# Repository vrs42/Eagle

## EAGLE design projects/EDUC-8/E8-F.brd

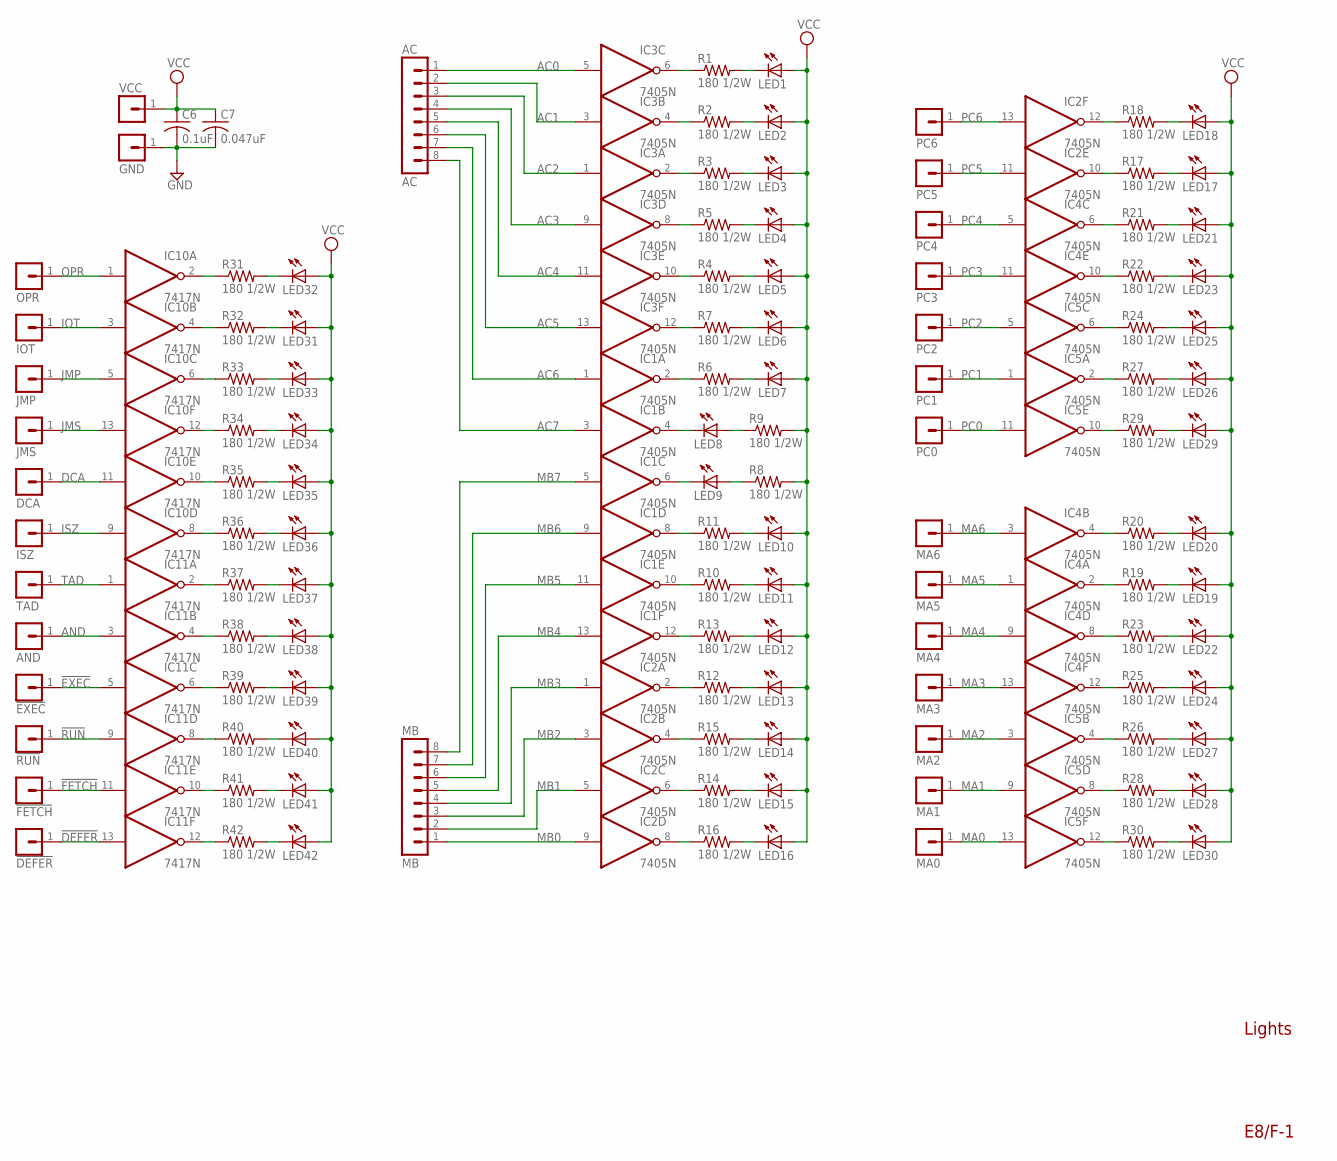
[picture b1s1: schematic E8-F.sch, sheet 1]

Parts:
!DEFER: MA01-1
!EXEC: MA01-1
!FETCH: MA01-1
!RUN: MA01-1
AC: AC; MA08-1
AND: MA01-1
C6: 0.1uF; C075-032X103
C7: 0.047uF; C075-032X103
DCA: MA01-1
GND: MA01-1
IC1, IC2, IC3, IC4, IC5: 7405N; DIL14
IC10, IC11: 7417N; DIL14
IOT: MA01-1
ISZ: MA01-1
JMP: MA01-1
JMS: MA01-1
LED1, LED2, LED3, LED4, LED5, LED6, LED7, LED8, LED9, LED10, LED11, LED12, LED13, LED14, LED15, LED16, LED17, LED18, LED19, LED20, LED21, LED22, LED23, LED24, LED25, LED26, LED27, LED28, LED29, LED30, LED31, LED32, LED33, LED34, LED35, LED36, LED37, LED38, LED39, LED40, LED41, LED42: LED5MM
MA0, MA1, MA2, MA3, MA4, MA5, MA6: MA01-1
MB: MB; MA08-1
OPR: MA01-1
PC0, PC1, PC2, PC3, PC4, PC5, PC6: MA01-1
R1, R2, R3, R5, R7, R10, R13, R14, R21, R28, R29, R30: 180 1/2W; 0309/.45
R4, R6, R8, R9, R12, R15, R16, R17, R18, R19, R24: 180 1/2W; 0309/12
R11: 180 1/2W; 0309/11
R20, R27: 180 1/2W; 0309/15
R22, R23, R25, R26, R39, R40, R41, R42: 180 1/2W; 0309/10
R31, R32, R33, R34, R35, R36, R37, R38: 180 1/2W; 0309/8
TAD: MA01-1
VCC: MA01-1

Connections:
!DEFER: !DEFER.1, IC11.13 (I)
!EXEC: !EXEC.1, IC11.5 (I)
!FETCH: !FETCH.1, IC11.11 (I)
!RUN: !RUN.1, IC11.9 (I)
AC0: AC.1, IC3.5 (I)
AC1: AC.2, IC3.3 (I)
AC2: AC.3, IC3.1 (I)
AC3: AC.4, IC3.9 (I)
AC4: AC.5, IC3.11 (I)
AC5: AC.6, IC3.13 (I)
AC6: AC.7, IC1.1 (I)
AC7: AC.8, IC1.3 (I)
AND: AND.1, IC11.3 (I)
DCA: DCA.1, IC10.11 (I)
GND: C6.2, C7.2, GND.1, IC1.7 (GND), IC2.7 (GND), IC3.7 (GND), IC4.7 (GND), IC5.7 (GND), IC10.7 (GND), IC11.7 (GND); also elsewhere on the board
IOT: IC10.3 (I), IOT.1
ISZ: IC10.9 (I), ISZ.1
JMP: IC10.5 (I), JMP.1
JMS: IC10.13 (I), JMS.1
MA0: IC5.13 (I), MA0.1
MA1: IC5.9 (I), MA1.1
MA2: IC5.3 (I), MA2.1
MA3: IC4.13 (I), MA3.1
MA4: IC4.9 (I), MA4.1
MA5: IC4.1 (I), MA5.1
MA6: IC4.3 (I), MA6.1
MB0: IC2.9 (I), MB.1
MB1: IC2.5 (I), MB.2
MB2: IC2.3 (I), MB.3
MB3: IC2.1 (I), MB.4
MB4: IC1.13 (I), MB.5
MB5: IC1.11 (I), MB.6
MB6: IC1.9 (I), MB.7
MB7: IC1.5 (I), MB.8
unnamed: IC2.12 (O), R18.1
unnamed: IC2.10 (O), R17.1
unnamed: IC3.6 (O), R1.1
unnamed: IC3.4 (O), R2.1
unnamed: IC3.2 (O), R3.1
unnamed: IC3.12 (O), R7.1
unnamed: LED7.K (C), R6.2
unnamed: LED12.K (C), R13.2
unnamed: IC1.10 (O), R10.1
unnamed: LED10.K (C), R11.2
unnamed: IC1.6 (O), LED9.K (C)
unnamed: LED8.A, R9.1
unnamed: IC1.2 (O), R6.1
unnamed: LED9.A, R8.1
unnamed: IC1.4 (O), LED8.K (C)
unnamed: IC1.8 (O), R11.1
unnamed: LED11.K (C), R10.2
unnamed: IC2.8 (O), R16.1
unnamed: LED13.K (C), R12.2
unnamed: LED18.K (C), R18.2
unnamed: LED17.K (C), R17.2
unnamed: LED16.K (C), R16.2
unnamed: LED15.K (C), R14.2
unnamed: LED14.K (C), R15.2
unnamed: IC2.6 (O), R14.1
unnamed: IC2.4 (O), R15.1
unnamed: IC2.2 (O), R12.1
unnamed: IC1.12 (O), R13.1
unnamed: IC3.10 (O), R4.1
unnamed: IC3.8 (O), R5.1
unnamed: LED1.K (C), R1.2
unnamed: LED6.K (C), R7.2
unnamed: LED5.K (C), R4.2
unnamed: LED4.K (C), R5.2
unnamed: LED3.K (C), R3.2
unnamed: LED2.K (C), R2.2
unnamed: LED25.K (C), R24.2
unnamed: LED19.K (C), R19.2
unnamed: LED24.K (C), R25.2
unnamed: LED23.K (C), R22.2
unnamed: LED22.K (C), R23.2
unnamed: LED21.K (C), R21.2
unnamed: IC5.6 (O), R24.1
unnamed: LED26.K (C), R27.2
unnamed: LED27.K (C), R26.2
unnamed: LED28.K (C), R28.2
unnamed: LED29.K (C), R29.2
unnamed: LED30.K (C), R30.2
unnamed: LED31.K (C), R32.2
unnamed: LED32.K (C), R31.2
unnamed: LED33.K (C), R33.2
unnamed: LED34.K (C), R34.2
unnamed: LED35.K (C), R35.2
unnamed: LED36.K (C), R36.2
unnamed: IC5.2 (O), R27.1
unnamed: IC5.12 (O), R30.1
unnamed: IC5.10 (O), R29.1
unnamed: IC5.8 (O), R28.1
unnamed: LED37.K (C), R37.2
unnamed: IC5.4 (O), R26.1
unnamed: LED40.K (C), R40.2
unnamed: LED39.K (C), R39.2
unnamed: LED38.K (C), R38.2
unnamed: LED42.K (C), R42.2
unnamed: LED41.K (C), R41.2
unnamed: IC10.2 (O), R31.1
unnamed: IC10.8 (O), R36.1
unnamed: IC10.10 (O), R35.1
unnamed: IC10.12 (O), R34.1
unnamed: IC10.6 (O), R33.1
unnamed: IC10.4 (O), R32.1
unnamed: IC11.2 (O), R37.1
unnamed: IC11.12 (O), R42.1
unnamed: IC11.10 (O), R41.1
unnamed: IC11.8 (O), R40.1
unnamed: IC11.6 (O), R39.1
unnamed: IC11.4 (O), R38.1
unnamed: LED20.K (C), R20.2
unnamed: IC4.2 (O), R19.1
unnamed: IC4.4 (O), R20.1
unnamed: IC4.6 (O), R21.1
unnamed: IC4.12 (O), R25.1
unnamed: IC4.10 (O), R22.1
unnamed: IC4.8 (O), R23.1
OPR: IC10.1 (I), OPR.1
PC0: IC5.11 (I), PC0.1
PC1: IC5.1 (I), PC1.1
PC2: IC5.5 (I), PC2.1
PC3: IC4.11 (I), PC3.1
PC4: IC4.5 (I), PC4.1
PC5: IC2.11 (I), PC5.1
PC6: IC2.13 (I), PC6.1
TAD: IC11.1 (I), TAD.1
VCC: C6.1, C7.1, IC1.14 (VCC), IC2.14 (VCC), IC3.14 (VCC), IC4.14 (VCC), IC5.14 (VCC), IC10.14 (VCC), IC11.14 (VCC), LED1.A, LED2.A, LED3.A, LED4.A, LED5.A, LED6.A, LED7.A, LED10.A, LED11.A, LED12.A, LED13.A, LED14.A, LED15.A, LED16.A, LED17.A, LED18.A, LED19.A, LED20.A, LED21.A, LED22.A, LED23.A, LED24.A, LED25.A, LED26.A, LED27.A, LED28.A, LED29.A, LED30.A, LED31.A, LED32.A, LED33.A, LED34.A, LED35.A, LED36.A, LED37.A, LED38.A, LED39.A, LED40.A, LED41.A, LED42.A, R8.2, R9.2, VCC.1; also elsewhere on the board

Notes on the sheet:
Lights
E8/F-1

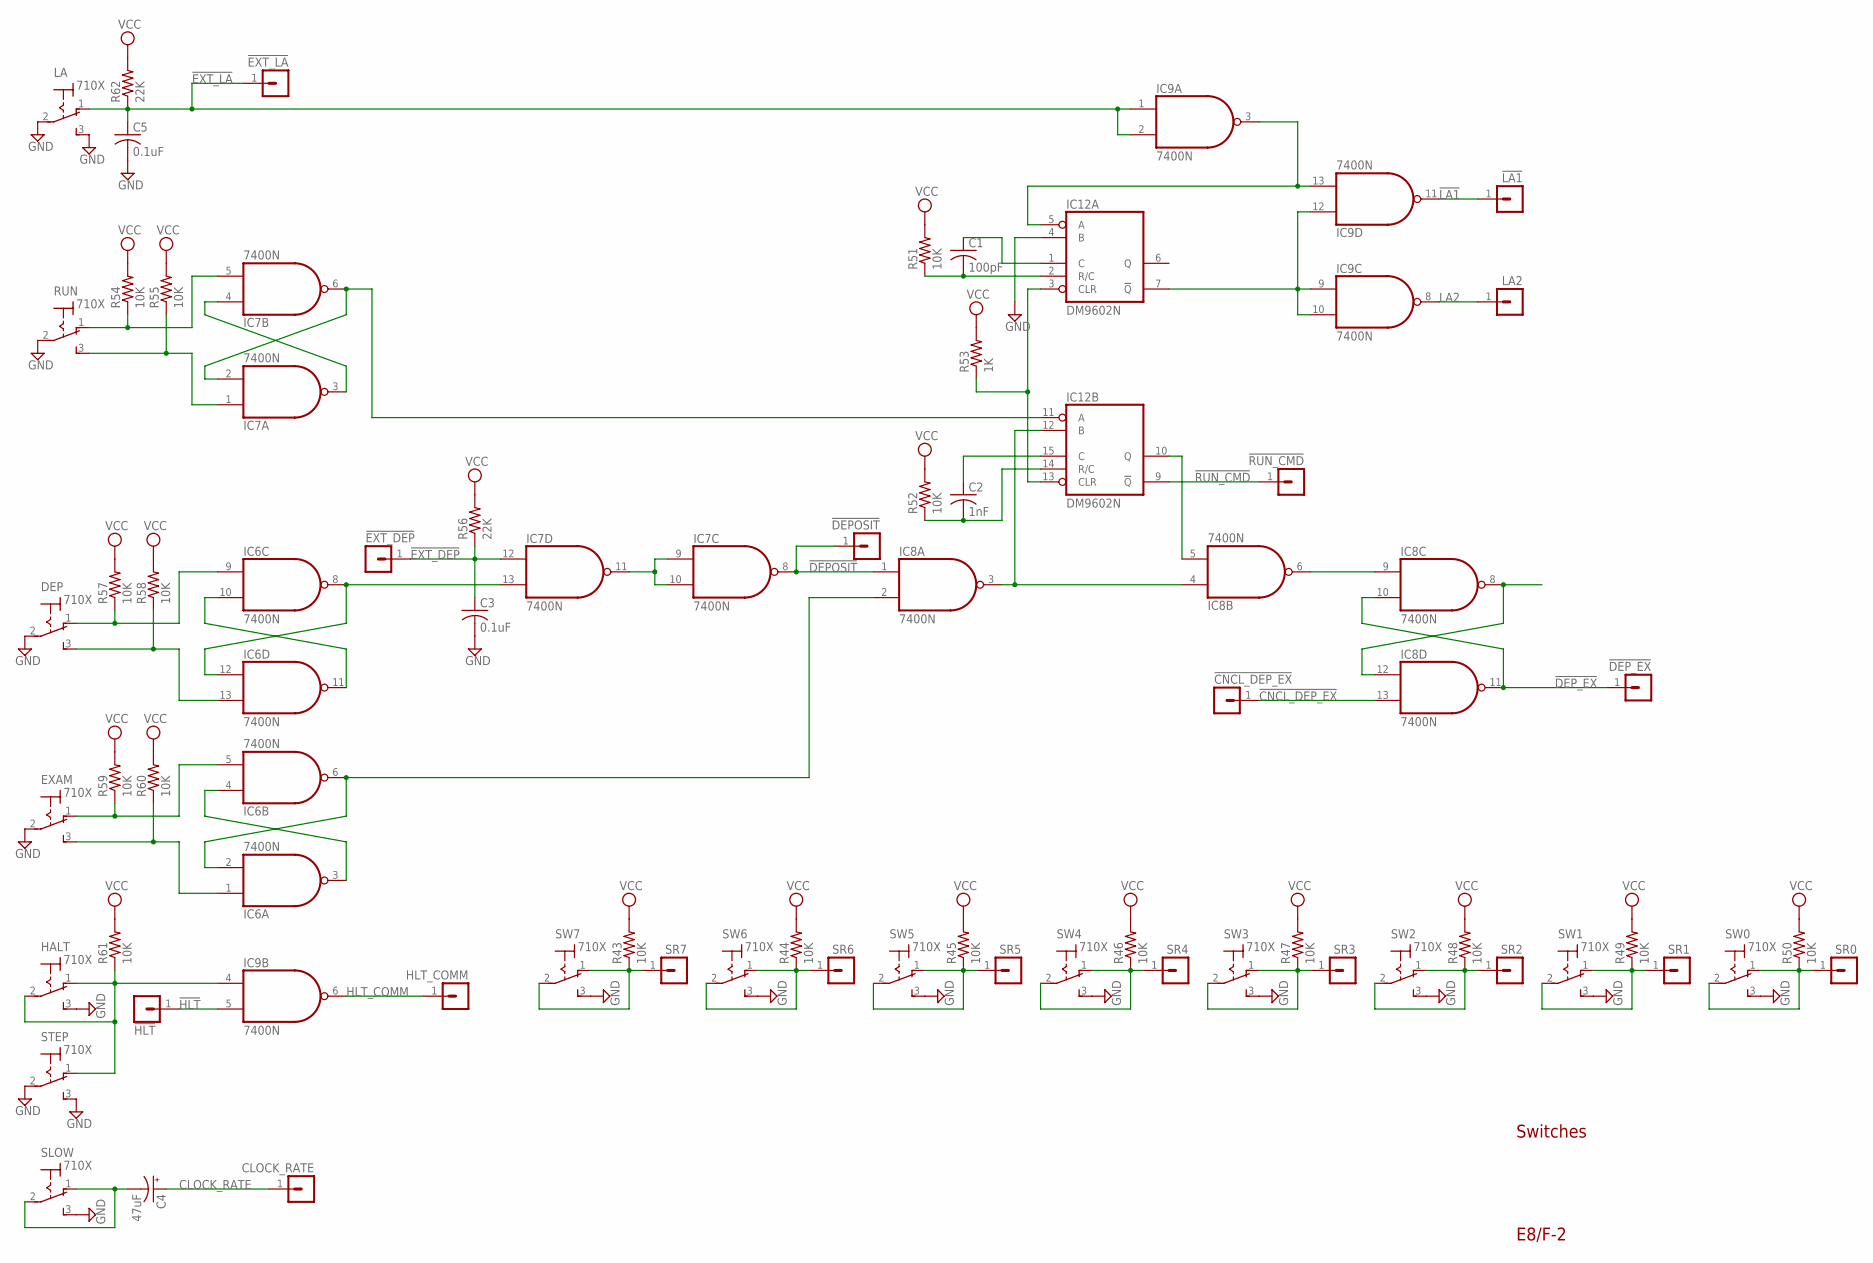
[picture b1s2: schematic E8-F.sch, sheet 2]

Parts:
!CNCL_DEP_EX: MA01-1
!DEPOSIT: MA01-1
!DEP_EX: MA01-1
!EXT_DEP: MA01-1
!EXT_LA: MA01-1
!HLT: MA01-1
!LA1: MA01-1
!RUN_CMD: MA01-1
C1: 100pF; C075-032X103
C2: 1nF; C075-032X103
C3: 0.1uF; C063-025X075
C4: 47uF; B45181C
C5: 0.1uF; C075-032X103
CLOCK_RATE: MA01-1
DEP: 710X; 7109
EXAM: 710X; 7109
HALT: 710X; 7109
HLT_COMM: MA01-1
IC6, IC7, IC8, IC9: 7400N; DIL14
IC12: DM9602N; DIL16
LA: 710X; 7109
LA2: MA01-1
R43, R44, R45, R46, R47, R48, R49, R50: 10K; 0207/12
R51: 10K; 0207/10
R52: 10K; 0207/15
R53: 1K; 0204/6
R54, R55, R57, R58, R59, R60: 10K; 0207/13
R56: 22K; 0207/10
R61: 10K; 0207/22
R62: 22K; 0207/13
RUN: 710X; 7109
SLOW: 710X; 7109
SR0, SR1, SR2, SR3, SR4, SR5, SR6, SR7: MA01-1
STEP: 710X; 7109
SW0, SW1, SW2, SW3, SW4, SW5, SW6, SW7: 710X; 7109

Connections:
!CNCL_DEP_EX: !CNCL_DEP_EX.1, IC8.13 (I1)
!DEPOSIT: !DEPOSIT.1, IC7.8 (O), IC8.1 (I0)
!DEP_EX: !DEP_EX.1, IC8.10 (I1), IC8.11 (O)
!EXT_DEP: !EXT_DEP.1, C3.1, IC7.12 (I0), R56.1
!EXT_LA: !EXT_LA.1, C5.1, IC9.1 (I0), IC9.2 (I1), LA.1 (O), R62.1
!HLT: !HLT.1, IC9.5 (I1)
!LA1: !LA1.1, IC9.11 (O)
!RUN_CMD: !RUN_CMD.1, IC12.9 (!Q)
CLOCK_RATE: C4.+, CLOCK_RATE.1
GND: C3.2, C5.2, DEP.2, EXAM.2, HALT.3 (S), IC6.7 (GND), IC7.7 (GND), IC8.7 (GND), IC9.7 (GND), IC12.4 (B), IC12.8 (GND), LA.2, LA.3 (S), RUN.2, SLOW.3 (S), STEP.2, STEP.3 (S), SW0.3 (S), SW1.3 (S), SW2.3 (S), SW3.3 (S), SW4.3 (S), SW5.3 (S), SW6.3 (S), SW7.3 (S); also elsewhere on the board
HALT: HALT.1 (O), HALT.2, IC9.4 (I0), R61.1, STEP.1 (O)
HLT_COMM: HLT_COMM.1, IC9.6 (O)
LA2: IC9.8 (O), LA2.1
unnamed: DEP.3 (S), IC6.13 (I1), R58.1
unnamed: IC6.3 (O), IC6.4 (I0)
unnamed: EXAM.1 (O), IC6.5 (I1), R59.1
unnamed: IC6.2 (I1), IC6.6 (O), IC8.2 (I1)
unnamed: EXAM.3 (S), IC6.1 (I0), R60.1
unnamed: IC8.6 (O), IC8.9 (I0)
unnamed: DEP.1 (O), IC6.9 (I0), R57.1
unnamed: IC6.10 (I1), IC6.11 (O)
unnamed: IC6.8 (O), IC6.12 (I0), IC7.13 (I1)
unnamed: IC7.1 (I0), R55.1, RUN.3 (S)
unnamed: IC7.2 (I1), IC7.6 (O), IC12.11 (A)
unnamed: IC7.3 (O), IC7.4 (I0)
unnamed: IC7.5 (I1), R54.1, RUN.1 (O)
unnamed: IC7.9 (I0), IC7.10 (I1), IC7.11 (O)
unnamed: IC8.3 (O), IC8.4 (I0), IC12.12 (B)
unnamed: IC8.5 (I1), IC12.10 (Q)
unnamed: IC8.8 (O), IC8.12 (I0)
unnamed: IC9.3 (O), IC9.13 (I1), IC12.5 (A)
unnamed: C2.2, IC12.14 (R/C), R52.1
unnamed: C1.2, IC12.2 (R/C), R51.1
unnamed: IC9.9 (I0), IC9.10 (I1), IC9.12 (I0), IC12.7 (!Q)
unnamed: C1.1, IC12.1 (C)
unnamed: C2.1, IC12.15 (C)
unnamed: IC12.3 (CLR), IC12.13 (CLR), R53.1
SLOW: C4.-, SLOW.1 (O), SLOW.2
SR0: R50.1, SR0.1, SW0.1 (O), SW0.2
SR1: R49.1, SR1.1, SW1.1 (O), SW1.2
SR2: R48.1, SR2.1, SW2.1 (O), SW2.2
SR3: R47.1, SR3.1, SW3.1 (O), SW3.2
SR4: R46.1, SR4.1, SW4.1 (O), SW4.2
SR5: R45.1, SR5.1, SW5.1 (O), SW5.2
SR6: R44.1, SR6.1, SW6.1 (O), SW6.2
SR7: R43.1, SR7.1, SW7.1 (O), SW7.2
VCC: IC6.14 (VCC), IC7.14 (VCC), IC8.14 (VCC), IC9.14 (VCC), IC12.16 (VCC), R43.2, R44.2, R45.2, R46.2, R47.2, R48.2, R49.2, R50.2, R51.2, R52.2, R53.2, R54.2, R55.2, R56.2, R57.2, R58.2, R59.2, R60.2, R61.2, R62.2; also elsewhere on the board

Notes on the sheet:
Switches
E8/F-2

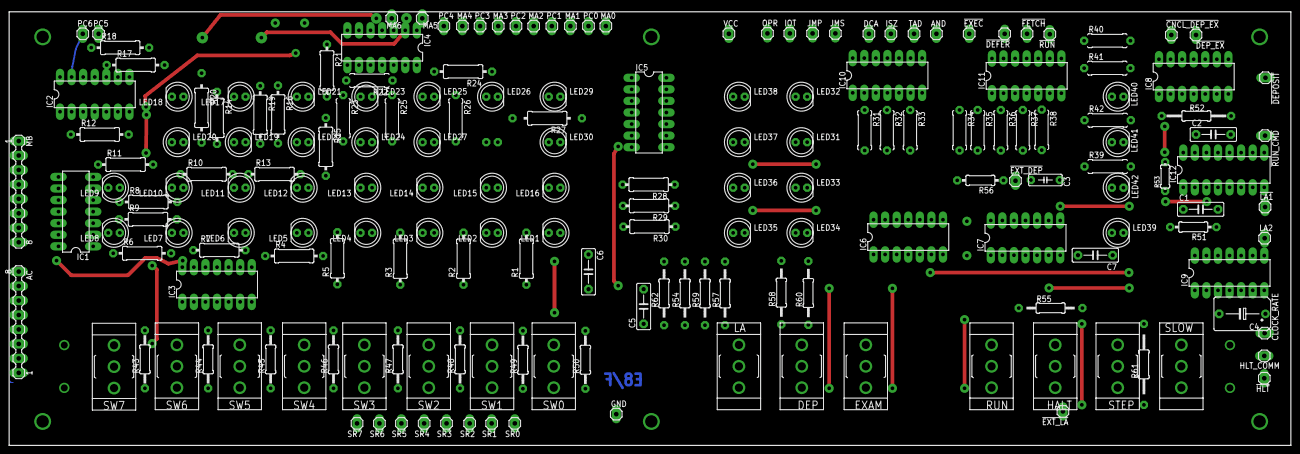
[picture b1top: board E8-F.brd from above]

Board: 2 copper layers, 281.3 x 95.2 mm, 187 parts (1 on the bottom side), 173 nets.

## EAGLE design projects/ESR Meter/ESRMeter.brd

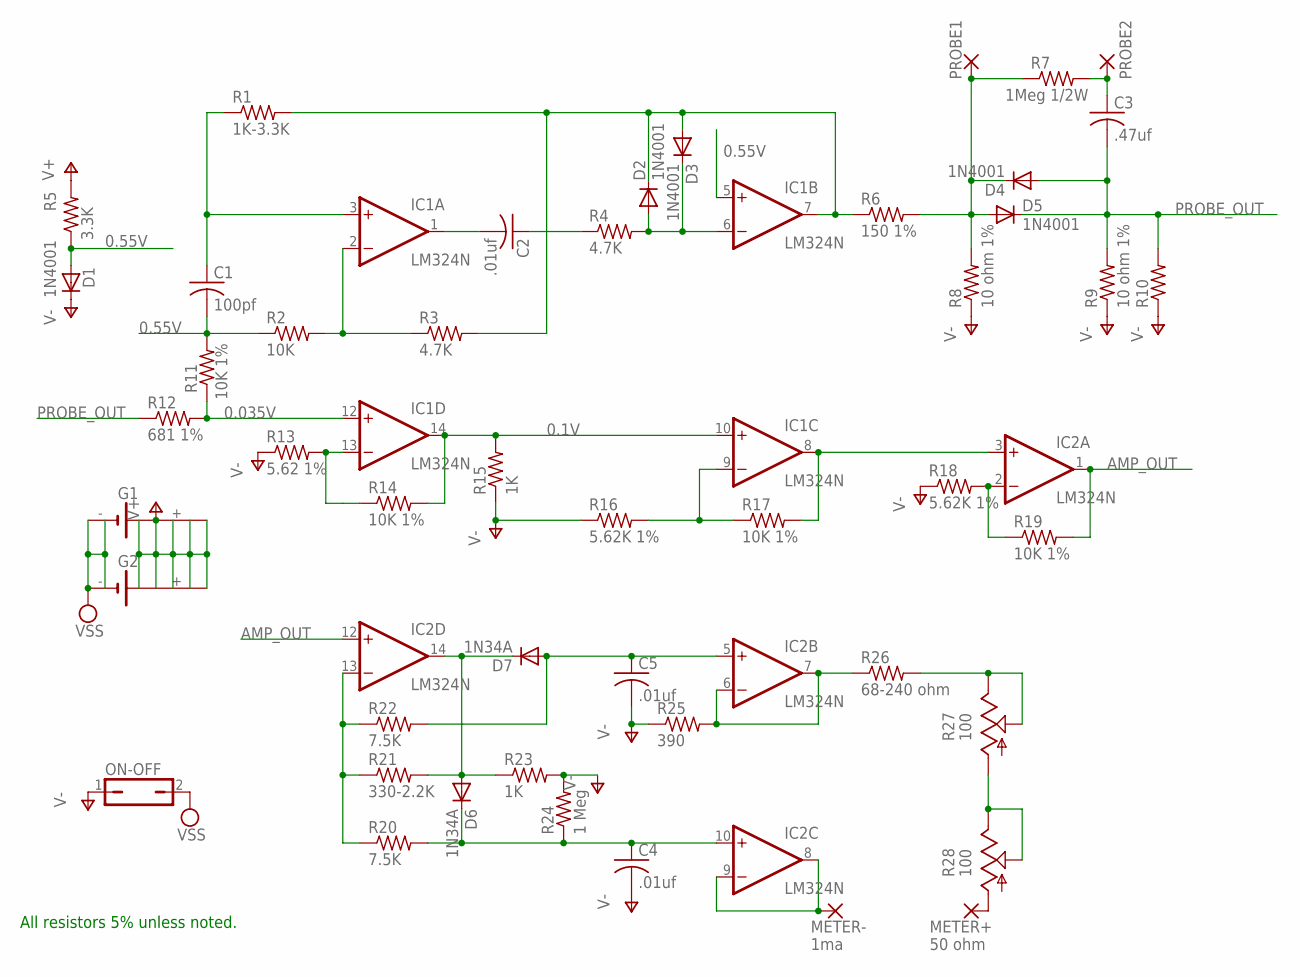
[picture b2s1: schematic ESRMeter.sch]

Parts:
C1: 100pf; C050-025X075
C2, C4, C5: .01uf; C050-025X075
C3: .47uf; C075-052X106
D1, D2, D3, D4, D5: 1N4001; DO41-10
D6, D7: 1N34A; DO41-10
G1, G2: B2430UNI
IC1, IC2: LM324N; DIL14
METER+: 50 ohm; 2,15/1,0
METER-: 1ma; 2,15/1,0
ON-OFF: JP1Q; JP1
PROBE1, PROBE2: 2,15/1,0
R1: 1K-3.3K; 0207/10
R2: 10K; 0207/10
R3, R4: 4.7K; 0207/10
R5: 3.3K; 0207/10
R6: 150 1%; 0207/10
R7: 1Meg 1/2W; 0207/12
R8, R9: 10 ohm 1%; 0207/10
R10: R-US_0207/10; 0207/10
R11, R14, R17, R19: 10K 1%; 0207/10
R12: 681 1%; 0207/10
R13: 5.62 1%; 0207/10
R15, R23: 1K; 0207/10
R16, R18: 5.62K 1%; 0207/10
R20, R22: 7.5K; 0207/10
R21: 330-2.2K; 0207/10
R24: 1 Meg; 0207/12
R25: 390; 0207/10
R26: 68-240 ohm; 0207/10
R27, R28: 100; B64W

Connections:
0.1V: IC1.10 (+IN), IC1.14 (OUT), R14.2, R15.2
0.035V: IC1.12 (+IN), R11.1, R12.2
0.55V: C1.2, D1.A, IC1.5 (+IN), R2.1, R5.1, R11.2
AMP_OUT: IC2.1 (OUT), IC2.12 (+IN), R19.2
unnamed: D4.C, D5.A, PROBE1.1, R6.2, R7.1, R8.2
unnamed: C1.1, IC1.3 (+IN), R1.1
unnamed: IC1.2 (-IN), R2.2, R3.1
unnamed: C2.2, IC1.1 (OUT)
unnamed: D2.C, D3.A, IC1.7 (OUT), R1.2, R3.2, R6.1
unnamed: C2.1, R4.1
unnamed: C3.1, PROBE2.1, R7.2
unnamed: D2.A, D3.C, IC1.6 (-IN), R4.2
unnamed: IC2.2 (-IN), R18.2, R19.1
unnamed: IC1.13 (-IN), R13.2, R14.1
unnamed: C5.1, D7.A, IC2.5 (+IN), R22.2
unnamed: IC1.8 (OUT), IC2.3 (+IN), R17.2
unnamed: IC1.9 (-IN), R16.2, R17.1
unnamed: IC2.13 (-IN), R20.1, R21.1, R22.1
unnamed: D6.A, D7.C, IC2.14 (OUT), R21.2, R23.1
unnamed: C4.1, D6.C, IC2.10 (+IN), R20.2, R24.1
unnamed: IC2.6 (-IN), IC2.7 (OUT), R25.2, R26.1
unnamed: IC2.8 (OUT), IC2.9 (-IN), METER-.1
unnamed: R26.2, R27.E, R27.S
unnamed: R27.A, R28.E, R28.S
unnamed: METER+.1, R28.A
PROBE_OUT: C3.2, D4.A, D5.C, R9.2, R10.2, R12.1
V+: G1.+, G1.+@1 (+), G1.+@2 (+), G1.+@3 (+), G1.+@4 (+), G2.+, G2.+@1 (+), G2.+@2 (+), G2.+@3 (+), G2.+@4 (+), IC1.4 (V+), IC2.4 (V+), R5.2
V-: C4.2, C5.2, D1.C, IC1.11 (V-), IC2.11 (V-), ON-OFF.1, R8.1, R9.1, R10.1, R13.1, R15.1, R16.1, R18.1, R23.2, R24.2, R25.1
VSS: G1.-, G1.-@1 (-), G2.-, G2.-@1 (-), ON-OFF.2

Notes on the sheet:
All resistors 5% unless noted.

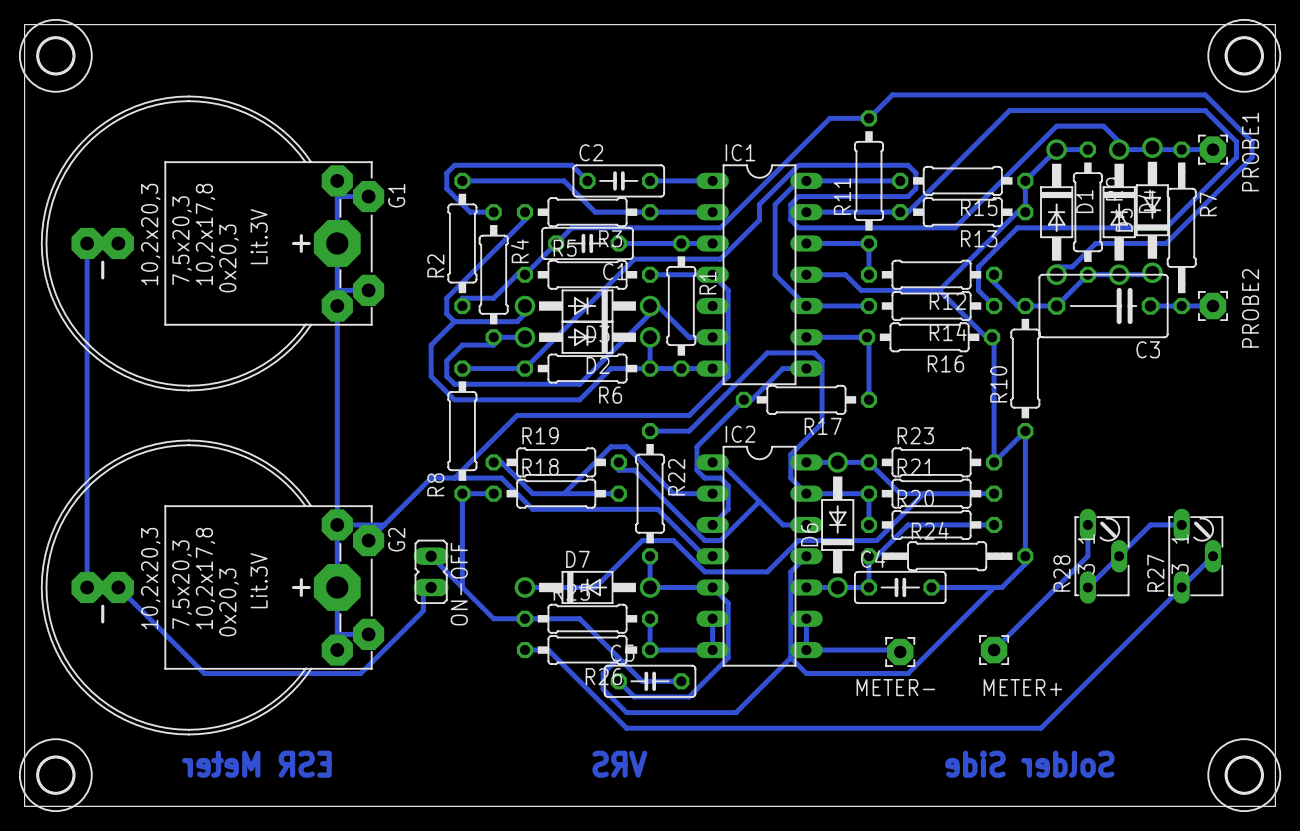
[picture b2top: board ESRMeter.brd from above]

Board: 2 copper layers, 101.6 x 63.5 mm, 53 parts (0 on the bottom side), 29 nets.

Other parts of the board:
U$1, U$2, U$3, U$4: 2,8

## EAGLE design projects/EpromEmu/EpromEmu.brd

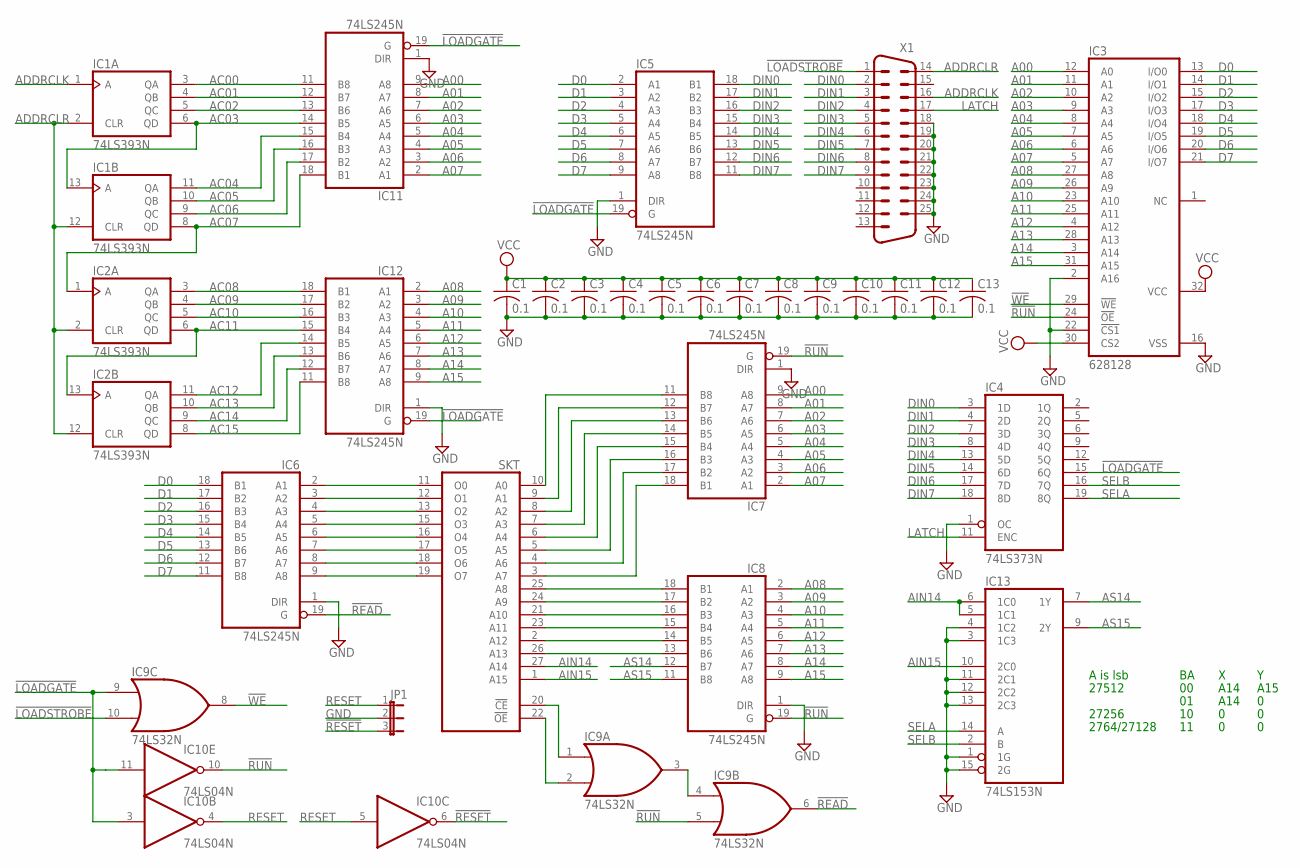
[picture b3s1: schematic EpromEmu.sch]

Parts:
C1, C2, C3, C4, C5, C6, C7, C8, C9, C10, C11, C12, C13: 0.1; C050-025X075
IC1, IC2: 74LS393N; DIL14
IC3: 628128; DIL32
IC4: 74LS373N; DIL20
IC5, IC6, IC7, IC8, IC11, IC12: 74LS245N; DIL20
IC9: 74LS32N; DIL14
IC10: 74LS04N; DIL14
IC13: 74LS153N; DIL16
JP1: JP2E; JP2
SKT: 27512; DIL28
X1: M25HP

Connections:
!LOADGATE: IC4.15 (6Q), IC5.19 (G), IC9.9 (I0), IC10.3 (I), IC10.11 (I), IC11.19 (G), IC12.19 (G)
!LOADSTROBE: IC9.10 (I1), X1.1
!READ: IC6.19 (G), IC9.6 (O)
!RESET: IC10.6 (O), JP1.3
!RUN: IC3.24 (!OE), IC7.19 (G), IC8.19 (G), IC9.5 (I1), IC10.10 (O)
!WE: IC3.29 (!WE), IC9.8 (O)
A00: IC3.12 (A0), IC7.9 (A8), IC11.9 (A8)
A01: IC3.11 (A1), IC7.8 (A7), IC11.8 (A7)
A02: IC3.10 (A2), IC7.7 (A6), IC11.7 (A6)
A03: IC3.9 (A3), IC7.6 (A5), IC11.6 (A5)
A04: IC3.8 (A4), IC7.5 (A4), IC11.5 (A4)
A05: IC3.7 (A5), IC7.4 (A3), IC11.4 (A3)
A06: IC3.6 (A6), IC7.3 (A2), IC11.3 (A2)
A07: IC3.5 (A7), IC7.2 (A1), IC11.2 (A1)
A08: IC3.27 (A8), IC8.2 (A1), IC12.2 (A1)
A09: IC3.26 (A9), IC8.3 (A2), IC12.3 (A2)
A10: IC3.23 (A10), IC8.4 (A3), IC12.4 (A3)
A11: IC3.25 (A11), IC8.5 (A4), IC12.5 (A4)
A12: IC3.4 (A12), IC8.6 (A5), IC12.6 (A5)
A13: IC3.28 (A13), IC8.7 (A6), IC12.7 (A6)
A14: IC3.3 (A14), IC8.8 (A7), IC12.8 (A7)
A15: IC3.31 (A15), IC8.9 (A8), IC12.9 (A8)
AC00: IC1.3 (QA), IC11.11 (B8)
AC01: IC1.4 (QB), IC11.12 (B7)
AC02: IC1.5 (QC), IC11.13 (B6)
AC03: IC1.6 (QD), IC1.13 (A), IC11.14 (B5)
AC04: IC1.11 (QA), IC11.15 (B4)
AC05: IC1.10 (QB), IC11.16 (B3)
AC06: IC1.9 (QC), IC11.17 (B2)
AC07: IC1.8 (QD), IC2.1 (A), IC11.18 (B1)
AC08: IC2.3 (QA), IC12.18 (B1)
AC09: IC2.4 (QB), IC12.17 (B2)
AC10: IC2.5 (QC), IC12.16 (B3)
AC11: IC2.6 (QD), IC2.13 (A), IC12.15 (B4)
AC12: IC2.11 (QA), IC12.14 (B5)
AC13: IC2.10 (QB), IC12.13 (B6)
AC14: IC2.9 (QC), IC12.12 (B7)
AC15: IC2.8 (QD), IC12.11 (B8)
ADDRCLK: IC1.1 (A), X1.16
ADDRCLR: IC1.2 (CLR), IC1.12 (CLR), IC2.2 (CLR), IC2.12 (CLR), X1.14
AIN14: IC13.5 (1C1), IC13.6 (1C0), SKT.27 (A14)
AIN15: IC13.10 (2C0), SKT.1 (A15)
AS14: IC8.12 (B7), IC13.7 (1Y)
AS15: IC8.11 (B8), IC13.9 (2Y)
D0: IC3.13 (I/O0), IC5.2 (A1), IC6.18 (B1)
D1: IC3.14 (I/O1), IC5.3 (A2), IC6.17 (B2)
D2: IC3.15 (I/O2), IC5.4 (A3), IC6.16 (B3)
D3: IC3.17 (I/O3), IC5.5 (A4), IC6.15 (B4)
D4: IC3.18 (I/O4), IC5.6 (A5), IC6.14 (B5)
D5: IC3.19 (I/O5), IC5.7 (A6), IC6.13 (B6)
D6: IC3.20 (I/O6), IC5.8 (A7), IC6.12 (B7)
D7: IC3.21 (I/O7), IC5.9 (A8), IC6.11 (B8)
DIN0: IC4.3 (1D), IC5.18 (B1), X1.2
DIN1: IC4.4 (2D), IC5.17 (B2), X1.3
DIN2: IC4.7 (3D), IC5.16 (B3), X1.4
DIN3: IC4.8 (4D), IC5.15 (B4), X1.5
DIN4: IC4.13 (5D), IC5.14 (B5), X1.6
DIN5: IC4.14 (6D), IC5.13 (B6), X1.7
DIN6: IC4.17 (7D), IC5.12 (B7), X1.8
DIN7: IC4.18 (8D), IC5.11 (B8), X1.9
GND: C1.2, C2.2, C3.2, C4.2, C5.2, C6.2, C7.2, C8.2, C9.2, C10.2, C11.2, C12.2, C13.2, IC1.7 (GND), IC2.7 (GND), IC3.2 (A16), IC3.16 (VSS), IC3.22 (!CS1), IC4.1 (OC), IC4.10 (GND), IC5.1 (DIR), IC5.10 (GND), IC6.1 (DIR), IC6.10 (GND), IC7.1 (DIR), IC7.10 (GND), IC8.1 (DIR), IC8.10 (GND), IC9.7 (GND), IC10.7 (GND), IC11.1 (DIR), IC11.10 (GND), IC12.1 (DIR), IC12.10 (GND), IC13.1 (1G), IC13.3 (1C3), IC13.4 (1C2), IC13.8 (GND), IC13.11 (2C1), IC13.12 (2C2), IC13.13 (2C3), IC13.15 (2G), JP1.2, SKT.14 (GND), X1.18, X1.19, X1.20, X1.21, X1.22, X1.23, X1.24, X1.25
LATCH: IC4.11 (ENC), X1.17
unnamed: IC6.2 (A1), SKT.11 (O0)
unnamed: IC6.3 (A2), SKT.12 (O1)
unnamed: IC6.4 (A3), SKT.13 (O2)
unnamed: IC6.5 (A4), SKT.15 (O3)
unnamed: IC6.6 (A5), SKT.16 (O4)
unnamed: IC6.7 (A6), SKT.17 (O5)
unnamed: IC6.8 (A7), SKT.18 (O6)
unnamed: IC6.9 (A8), SKT.19 (O7)
unnamed: IC9.2 (I1), SKT.22 (!OE)
unnamed: IC9.1 (I0), SKT.20 (!CE)
unnamed: IC8.13 (B6), SKT.26 (A13)
unnamed: IC8.14 (B5), SKT.2 (A12)
unnamed: IC8.15 (B4), SKT.23 (A11)
unnamed: IC8.16 (B3), SKT.21 (A10)
unnamed: IC8.17 (B2), SKT.24 (A9)
unnamed: IC8.18 (B1), SKT.25 (A8)
unnamed: IC7.18 (B1), SKT.3 (A7)
unnamed: IC7.17 (B2), SKT.4 (A6)
unnamed: IC7.16 (B3), SKT.5 (A5)
unnamed: IC7.15 (B4), SKT.6 (A4)
unnamed: IC7.14 (B5), SKT.7 (A3)
unnamed: IC7.13 (B6), SKT.8 (A2)
unnamed: IC7.12 (B7), SKT.9 (A1)
unnamed: IC7.11 (B8), SKT.10 (A0)
unnamed: IC9.3 (O), IC9.4 (I0)
RESET: IC10.4 (O), IC10.5 (I), JP1.1
SELA: IC4.19 (8Q), IC13.14 (A)
SELB: IC4.16 (7Q), IC13.2 (B)
VCC: C1.1, C2.1, C3.1, C4.1, C5.1, C6.1, C7.1, C8.1, C9.1, C10.1, C11.1, C12.1, C13.1, IC1.14 (VCC), IC2.14 (VCC), IC3.30 (CS2), IC3.32 (VCC), IC4.20 (VCC), IC5.20 (VCC), IC6.20 (VCC), IC7.20 (VCC), IC8.20 (VCC), IC9.14 (VCC), IC10.14 (VCC), IC11.20 (VCC), IC12.20 (VCC), IC13.16 (VCC), SKT.28 (VCC)

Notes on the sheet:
A is lsb
A14
A15
27512
27256
2764/27128

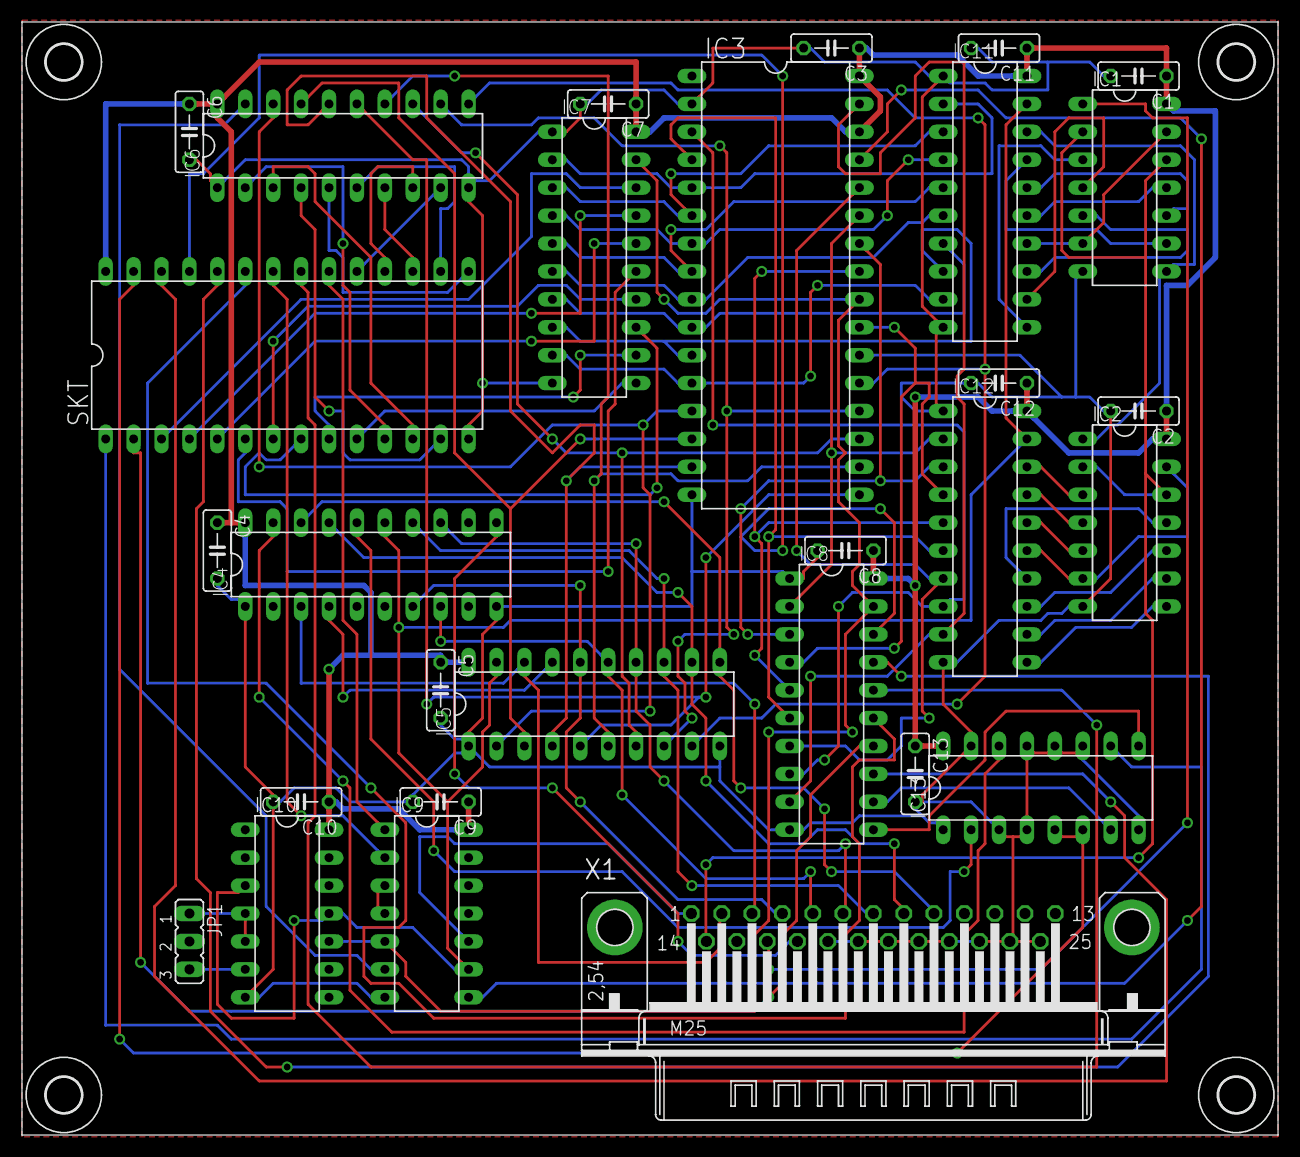
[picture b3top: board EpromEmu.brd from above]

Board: 2 copper layers, 114.3 x 101.3 mm, 33 parts (0 on the bottom side), 91 nets.

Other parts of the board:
U$1, U$2, U$3, U$4: 3,2
